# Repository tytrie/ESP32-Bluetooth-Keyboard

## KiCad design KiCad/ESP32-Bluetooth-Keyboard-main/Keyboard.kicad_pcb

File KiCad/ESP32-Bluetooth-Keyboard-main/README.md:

Documentation for ESP32 based bluetooth mechanical keyboard

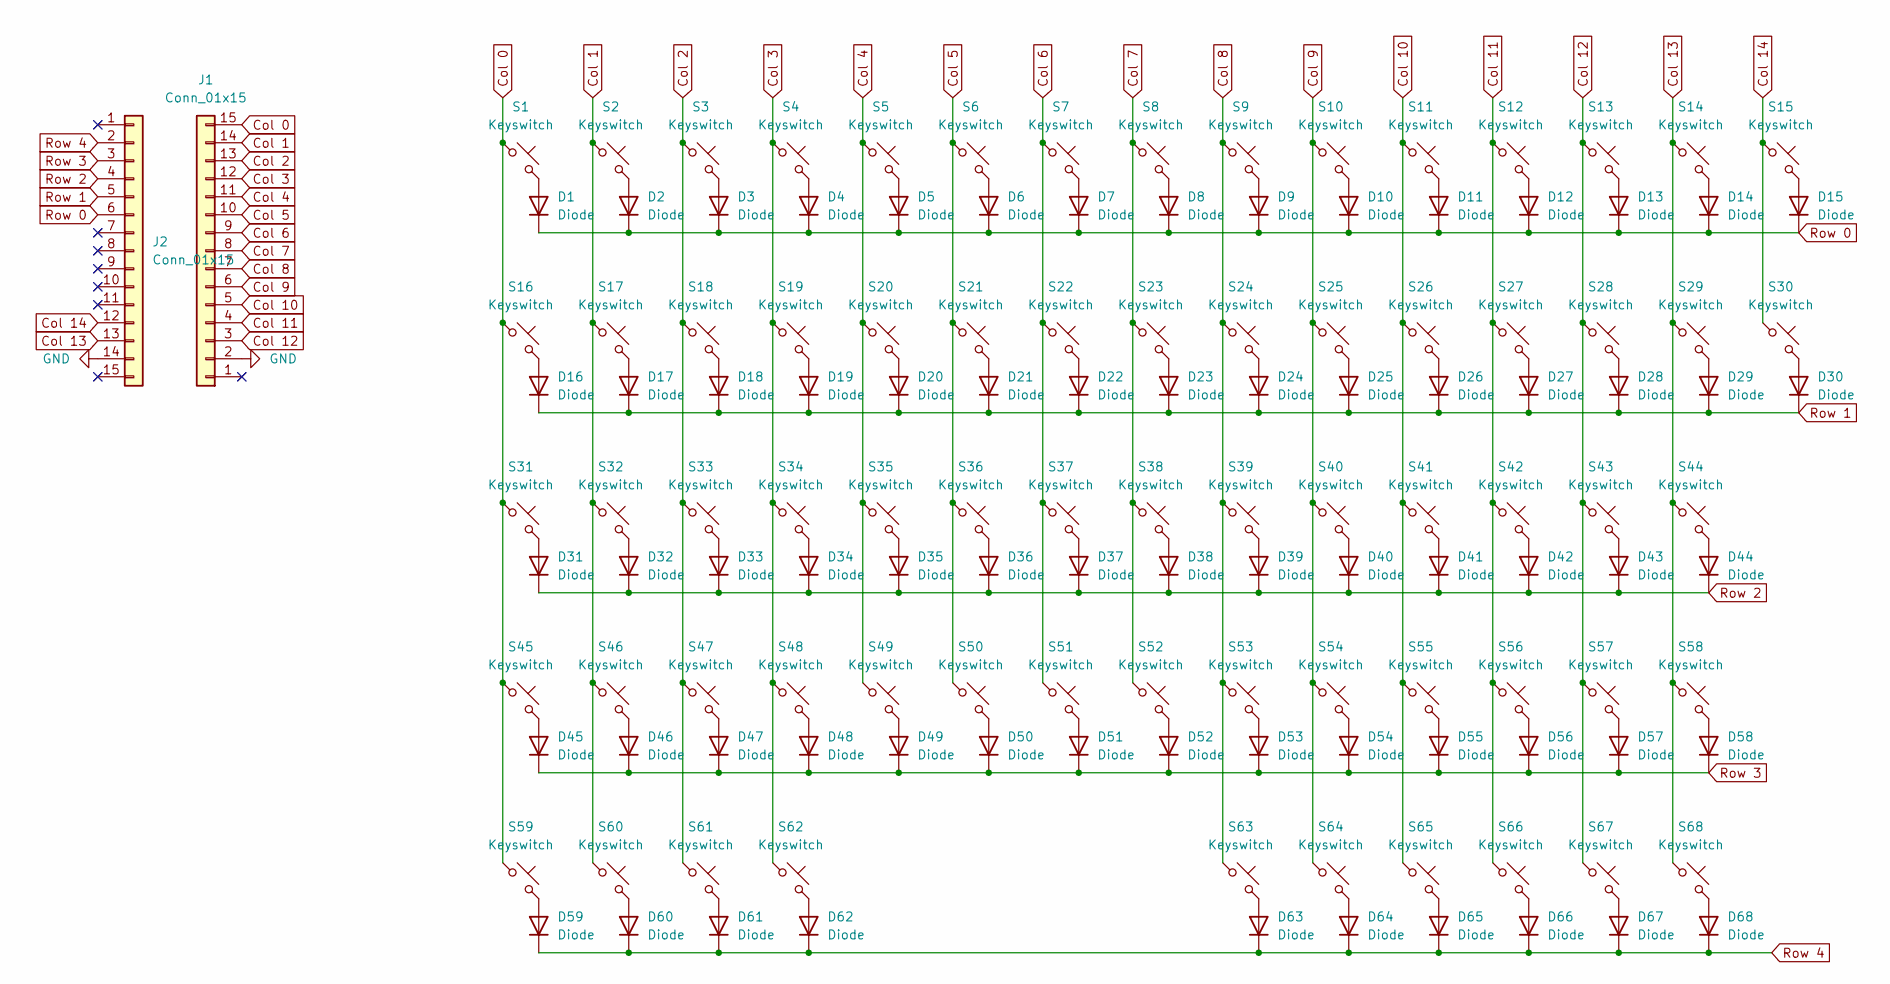
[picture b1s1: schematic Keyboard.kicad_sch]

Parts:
D1, D2, D3, D4, D5, D6, D7, D8, D9, D10, D11, D12, D13, D14, D15, D16, D17, D18, D19, D20, D21, D22, D23, D24, D25, D26, D27, D28, D29, D30, D31, D32, D33, D34, D35, D36, D37, D38, D39, D40, D41, D42, D43, D44, D45, D46, D47, D48, D49, D50, D51, D52, D53, D54, D55, D56, D57, D58, D59, D60, D61, D62, D63, D64, D65, D66, D67, D68: Diode; Diode_DO-35
J1, J2: Conn_01x15; JST_PH_B15B-PH-K_1x15_P2.00mm_Vertical
S1, S2, S3, S4, S5, S6, S7, S8, S9, S10, S11, S12, S13, S14, S15, S16, S17, S18, S19, S20, S21, S22, S23, S24, S25, S26, S27, S28, S29, S30, S31, S32, S33, S34, S35, S36, S37, S38, S39, S40, S41, S42, S43, S44, S45, S46, S47, S48, S49, S50, S51, S52, S53, S54, S55, S56, S57, S58, S59, S60, S61, S62, S63, S64, S65, S66, S67, S68: Keyswitch; MX_PCB_1.00u

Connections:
Col 0: J1.15, S1.1, S16.1, S31.1, S45.1, S59.1
Col 1: J1.14, S2.1, S17.1, S32.1, S46.1, S60.1
Col 2: J1.13, S3.1, S18.1, S33.1, S47.1, S61.1
Col 3: J1.12, S4.1, S19.1, S34.1, S48.1, S62.1
Col 4: J1.11, S5.1, S20.1, S35.1, S49.1
Col 5: J1.10, S6.1, S21.1, S36.1, S50.1
Col 6: J1.9, S7.1, S22.1, S37.1, S51.1
Col 7: J1.8, S8.1, S23.1, S38.1, S52.1
Col 8: J1.7, S9.1, S24.1, S39.1, S53.1, S63.1
Col 9: J1.6, S10.1, S25.1, S40.1, S54.1, S64.1
Col 10: J1.5, S11.1, S26.1, S41.1, S55.1, S65.1
Col 11: J1.4, S12.1, S27.1, S42.1, S56.1, S66.1
Col 12: J1.3, S13.1, S28.1, S43.1, S57.1, S67.1
Col 13: J2.13, S14.1, S29.1, S44.1, S58.1, S68.1
Col 14: J2.12, S15.1, S30.1
GND: J1.2, J2.14
unnamed: D1.2 (A), S1.2
unnamed: D2.2 (A), S2.2
unnamed: D3.2 (A), S3.2
unnamed: D4.2 (A), S4.2
unnamed: D5.2 (A), S5.2
unnamed: D6.2 (A), S6.2
unnamed: D7.2 (A), S7.2
unnamed: D8.2 (A), S8.2
unnamed: D9.2 (A), S9.2
unnamed: D10.2 (A), S10.2
unnamed: D11.2 (A), S11.2
unnamed: D12.2 (A), S12.2
unnamed: D13.2 (A), S13.2
unnamed: D14.2 (A), S14.2
unnamed: D15.2 (A), S15.2
unnamed: D16.2 (A), S16.2
unnamed: D17.2 (A), S17.2
unnamed: D18.2 (A), S18.2
unnamed: D19.2 (A), S19.2
unnamed: D20.2 (A), S20.2
unnamed: D21.2 (A), S21.2
unnamed: D22.2 (A), S22.2
unnamed: D23.2 (A), S23.2
unnamed: D24.2 (A), S24.2
unnamed: D25.2 (A), S25.2
unnamed: D26.2 (A), S26.2
unnamed: D27.2 (A), S27.2
unnamed: D28.2 (A), S28.2
unnamed: D29.2 (A), S29.2
unnamed: D30.2 (A), S30.2
unnamed: D31.2 (A), S31.2
unnamed: D32.2 (A), S32.2
unnamed: D33.2 (A), S33.2
unnamed: D34.2 (A), S34.2
unnamed: D35.2 (A), S35.2
unnamed: D36.2 (A), S36.2
unnamed: D37.2 (A), S37.2
unnamed: D38.2 (A), S38.2
unnamed: D39.2 (A), S39.2
unnamed: D40.2 (A), S40.2
unnamed: D41.2 (A), S41.2
unnamed: D42.2 (A), S42.2
unnamed: D43.2 (A), S43.2
unnamed: D44.2 (A), S44.2
unnamed: D45.2 (A), S45.2
unnamed: D46.2 (A), S46.2
unnamed: D47.2 (A), S47.2
unnamed: D48.2 (A), S48.2
unnamed: D49.2 (A), S49.2
unnamed: D50.2 (A), S50.2
unnamed: D51.2 (A), S51.2
unnamed: D52.2 (A), S52.2
unnamed: D53.2 (A), S53.2
unnamed: D54.2 (A), S54.2
unnamed: D55.2 (A), S55.2
unnamed: D56.2 (A), S56.2
unnamed: D57.2 (A), S57.2
unnamed: D58.2 (A), S58.2
unnamed: D59.2 (A), S59.2
unnamed: D60.2 (A), S60.2
unnamed: D61.2 (A), S61.2
unnamed: D62.2 (A), S62.2
unnamed: D63.2 (A), S63.2
unnamed: D64.2 (A), S64.2
unnamed 80: D65.2 (A), S65.2; also elsewhere on the board
unnamed 81: D66.2 (A), S66.2; also elsewhere on the board
unnamed 82: D67.2 (A), S67.2; also elsewhere on the board
unnamed 83: D68.2 (A), S68.2; also elsewhere on the board
Row 0: D1.1 (K), D2.1 (K), D3.1 (K), D4.1 (K), D5.1 (K), D6.1 (K), D7.1 (K), D8.1 (K), D9.1 (K), D10.1 (K), D11.1 (K), D12.1 (K), D13.1 (K), D14.1 (K), D15.1 (K), J2.6
Row 1: D16.1 (K), D17.1 (K), D18.1 (K), D19.1 (K), D20.1 (K), D21.1 (K), D22.1 (K), D23.1 (K), D24.1 (K), D25.1 (K), D26.1 (K), D27.1 (K), D28.1 (K), D29.1 (K), D30.1 (K), J2.5
Row 2: D31.1 (K), D32.1 (K), D33.1 (K), D34.1 (K), D35.1 (K), D36.1 (K), D37.1 (K), D38.1 (K), D39.1 (K), D40.1 (K), D41.1 (K), D42.1 (K), D43.1 (K), D44.1 (K), J2.4
Row 3: D45.1 (K), D46.1 (K), D47.1 (K), D48.1 (K), D49.1 (K), D50.1 (K), D51.1 (K), D52.1 (K), D53.1 (K), D54.1 (K), D55.1 (K), D56.1 (K), D57.1 (K), D58.1 (K), J2.3

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
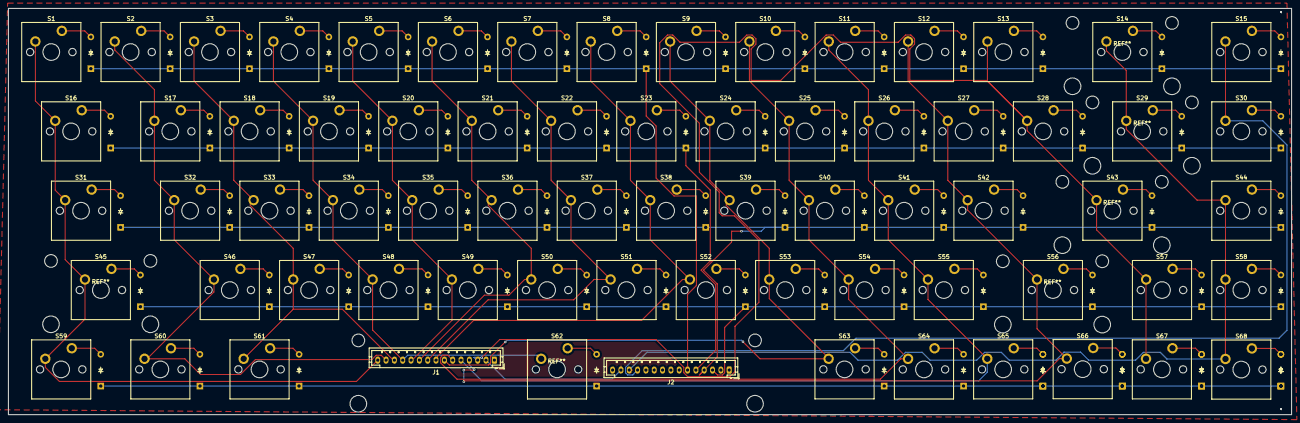
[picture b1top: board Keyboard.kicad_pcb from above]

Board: 2 copper layers, 308.1 x 97.5 mm, 142 parts (0 on the bottom side), 89 nets.

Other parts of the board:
D65#2, D66#2, D67#2, D68#2: Diode; Diode_DO-35

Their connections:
unnamed 80: D65#2.2 (A); also elsewhere on the board
unnamed 81: D66#2.2 (A); also elsewhere on the board
unnamed 82: D67#2.2 (A); also elsewhere on the board
unnamed 83: D68#2.2 (A); also elsewhere on the board

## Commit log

2024-11-25 README
2024-11-25 Kicad files
